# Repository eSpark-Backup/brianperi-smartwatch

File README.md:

# BrianPeri-SmartWatch
 To enhance existing Smart Watch Design and to add support for BLE / WiFi Capability

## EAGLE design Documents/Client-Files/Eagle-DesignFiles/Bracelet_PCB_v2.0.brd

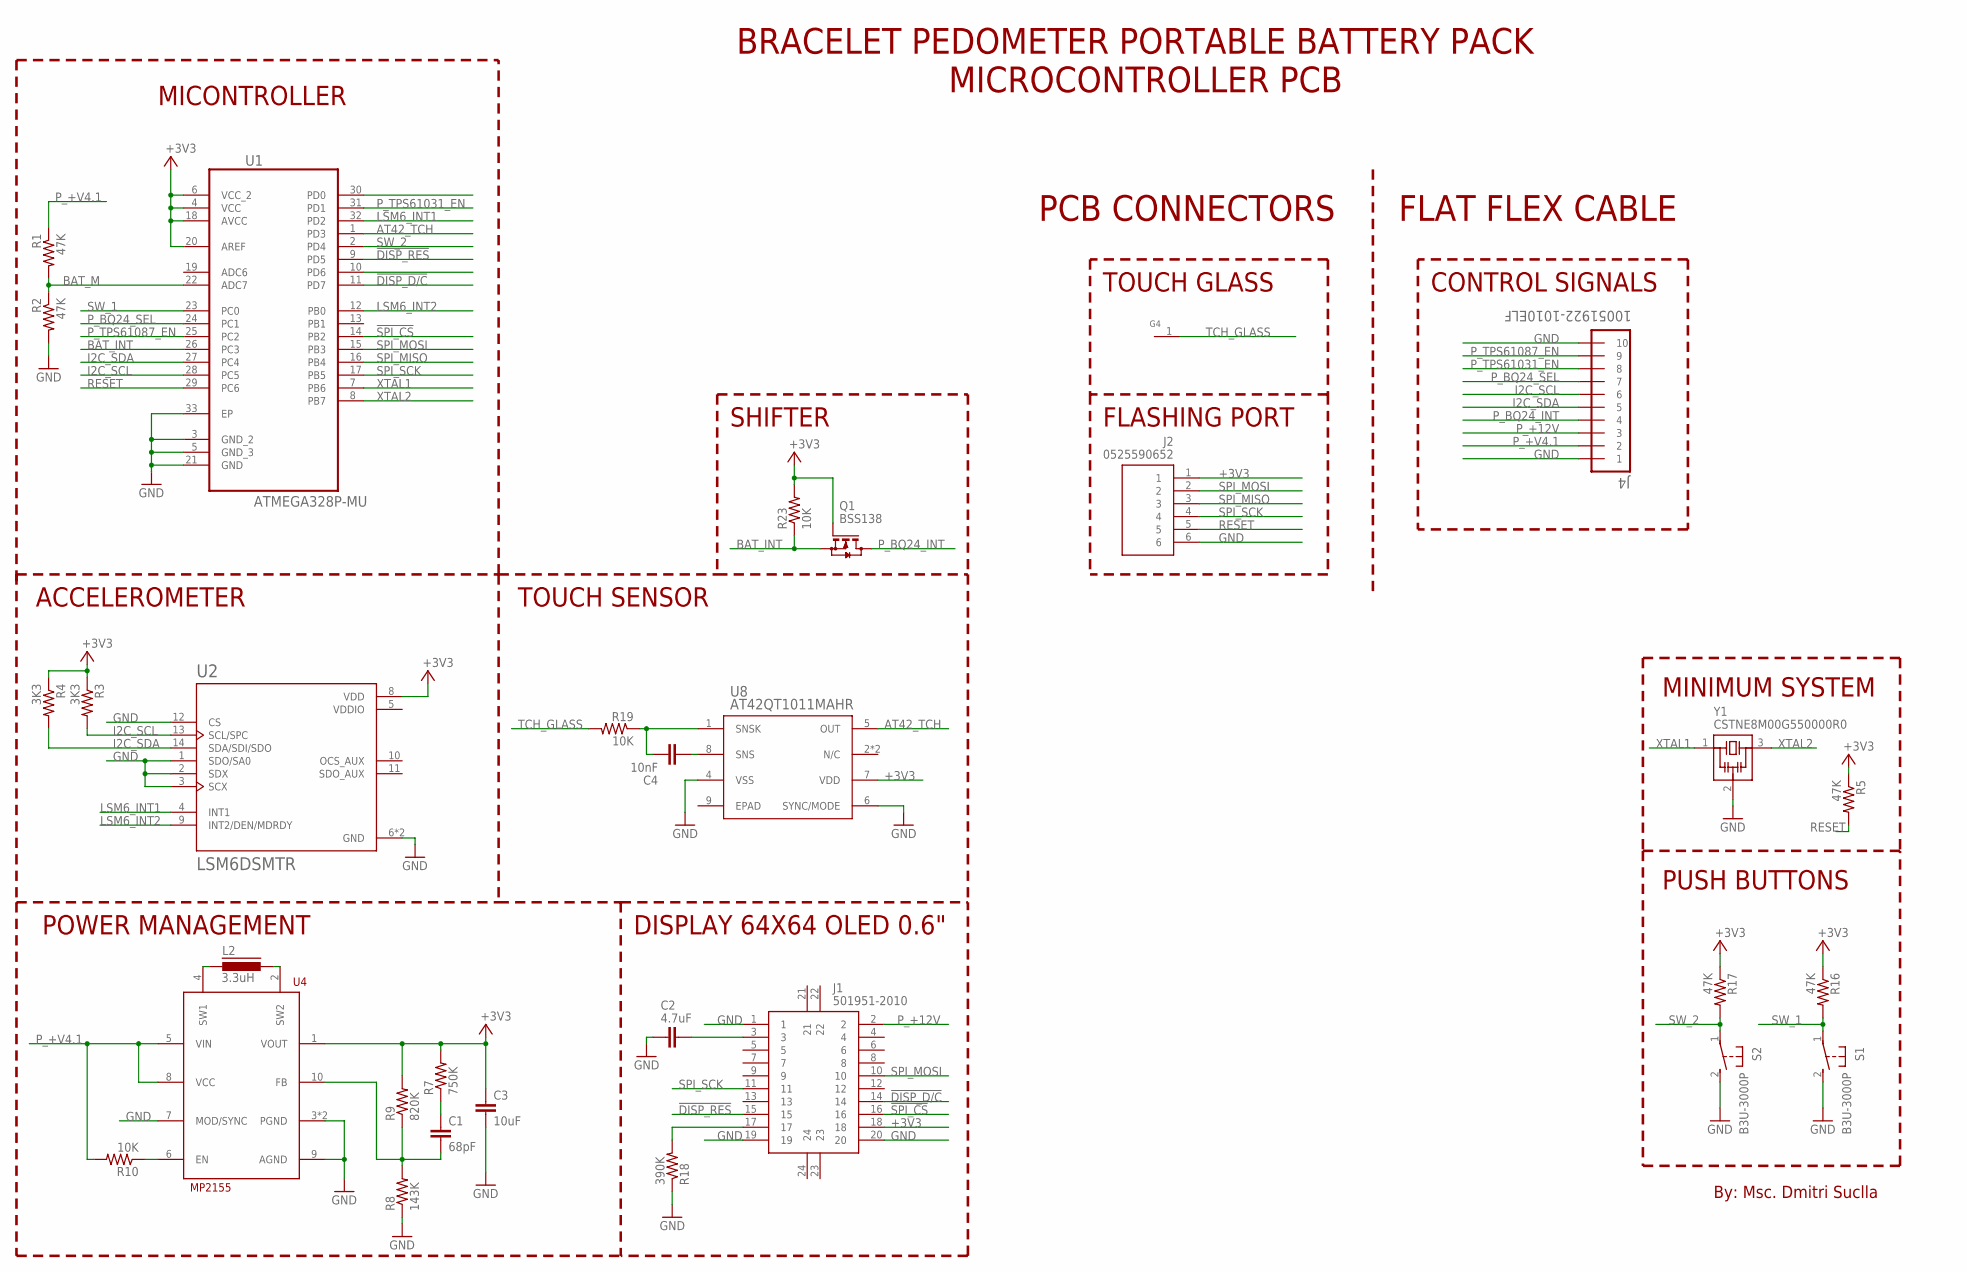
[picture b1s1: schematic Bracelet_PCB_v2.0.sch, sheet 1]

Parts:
C1: 68pF; C0201; MPN GRM0335C1H680JA01D
C2: 4.7uF; C0402
C3: 10uF; C0603; MPN GRM188R61C106KAALJ
C4: 10nF; C0201; MPN GRM033R61E103MA12D
G4: TOUCH_GLASS
J1: 501951-2010; 5019512010
J2: 0525590652
J4: 10051922-1010ELF; FCI_10051922-1010ELF
L2: 3.3uH; 0603(1608)
Q1: BSS138; SOT23
R1, R2, R5, R16, R17: 47K; R0201
R3, R4: 3K3; R0201
R7: 750K; R0201
R8: 143K; R0201
R9: 820K; R0201
R10, R19: 10K; R0201
R18: 390K; R0201
R23: 10K; R0201; MPN ERJ-1GNF1583C
S1, S2: B3U-3000P; SW_B3U-3000P
U1: ATMEGA328P-MU; QFN50P500X500X100-33N
U2: LSM6DSMTR; PQFN50P300X250X86-14N
U4: MP2155; QFN10
U8: AT42QT1011MAHR; 8-UDFN
Y1: CSTNE8M00G550000R0; CSTNE

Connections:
!DISP_D/C: J1.14, U1.11 (PD7)
!DISP_RES: J1.15, U1.9 (PD5)
!SPI_CS: J1.16, U1.14 (PB2)
+3V3: C3.1, J1.18, J2.1, Q1.1 (G), R3.1, R4.1, R5.1, R7.2, R9.2, R16.1, R17.1, R23.2, U1.4 (VCC), U1.6 (VCC_2), U1.18 (AVCC), U1.20 (AREF), U2.8 (VDD), U4.1 (VOUT), U8.7 (VDD)
AT42_TCH: U1.1 (PD3), U8.5 (OUT)
BAT_INT: Q1.2 (S), R23.1, U1.26 (PC3)
BAT_M: R1.2, R2.1, U1.22 (ADC7)
GND: C2.2, C3.2, J1.1, J1.19, J1.20, J2.6, J4.1, J4.10, R2.2, R8.1, R18.1, S1.2, S2.2, U1.3 (GND_2), U1.5 (GND_3), U1.21 (GND), U1.33 (EP), U2.1 (SDO/SA0), U2.2 (SDX), U2.3 (SCX), U2.6 (GND), U2.7 (GND), U2.12 (CS), U4.3 (PGND), U4.7 (MOD/SYNC), U4.9 (AGND), U4.EP (PGND), U8.4 (VSS), U8.6 (SYNC/MODE), Y1.2 (GND)
I2C_SCL: J4.6, R3.2, U1.28 (PC5), U2.13 (SCL/SPC)
I2C_SDA: J4.5, R4.2, U1.27 (PC4), U2.14 (SDA/SDI/SDO)
LSM6_INT1: U1.32 (PD2), U2.4 (INT1)
LSM6_INT2: U1.12 (PB0), U2.9 (INT2/DEN/MDRDY)
unnamed: C1.1, R7.1
unnamed: C1.2, R8.2, R9.1, U4.10 (FB)
unnamed: L2.2, U4.2 (SW2)
unnamed: L2.1, U4.4 (SW1)
unnamed: C4.1, U8.8 (SNS)
unnamed: C2.1, J1.3
unnamed: C4.2, R19.1, U8.1 (SNSK)
unnamed: R10.1, U4.6 (EN)
unnamed: J1.17, R18.2
P_+12V: J1.2, J4.3
P_+V4.1: J4.2, R1.1, R10.2, U4.5 (VIN), U4.8 (VCC)
P_BQ24_INT: J4.4, Q1.3 (D)
P_BQ24_SEL: J4.7, U1.24 (PC1)
P_TPS61031_EN: J4.8, U1.31 (PD1)
P_TPS61087_EN: J4.9, U1.25 (PC2)
RESET: J2.5, R5.2, U1.29 (PC6)
SPI_MISO: J2.3, U1.16 (PB4)
SPI_MOSI: J1.10, J2.2, U1.15 (PB3)
SPI_SCK: J1.11, J2.4, U1.17 (PB5)
SW_1: R16.2, S1.1, U1.23 (PC0)
SW_2: R17.2, S2.1, U1.2 (PD4)
TCH_GLASS: G4.1, R19.2
VDDIO: U2.5 (VDDIO)
XTAL1: U1.7 (PB6), Y1.1 (IN)
XTAL2: U1.8 (PB7), Y1.3 (OUT)

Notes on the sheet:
By: Msc. Dmitri Suclla
MINIMUM SYSTEM
ACCELEROMETER
POWER MANAGEMENT
DISPLAY 64X64 OLED 0.6"
MICONTROLLER
FLASHING PORT
PUSH BUTTONS
TOUCH SENSOR
BRACELET PEDOMETER PORTABLE BATTERY PACK
MICROCONTROLLER PCB
PCB CONNECTORS
CONTROL SIGNALS
FLAT FLEX CABLE
TOUCH GLASS
SHIFTER

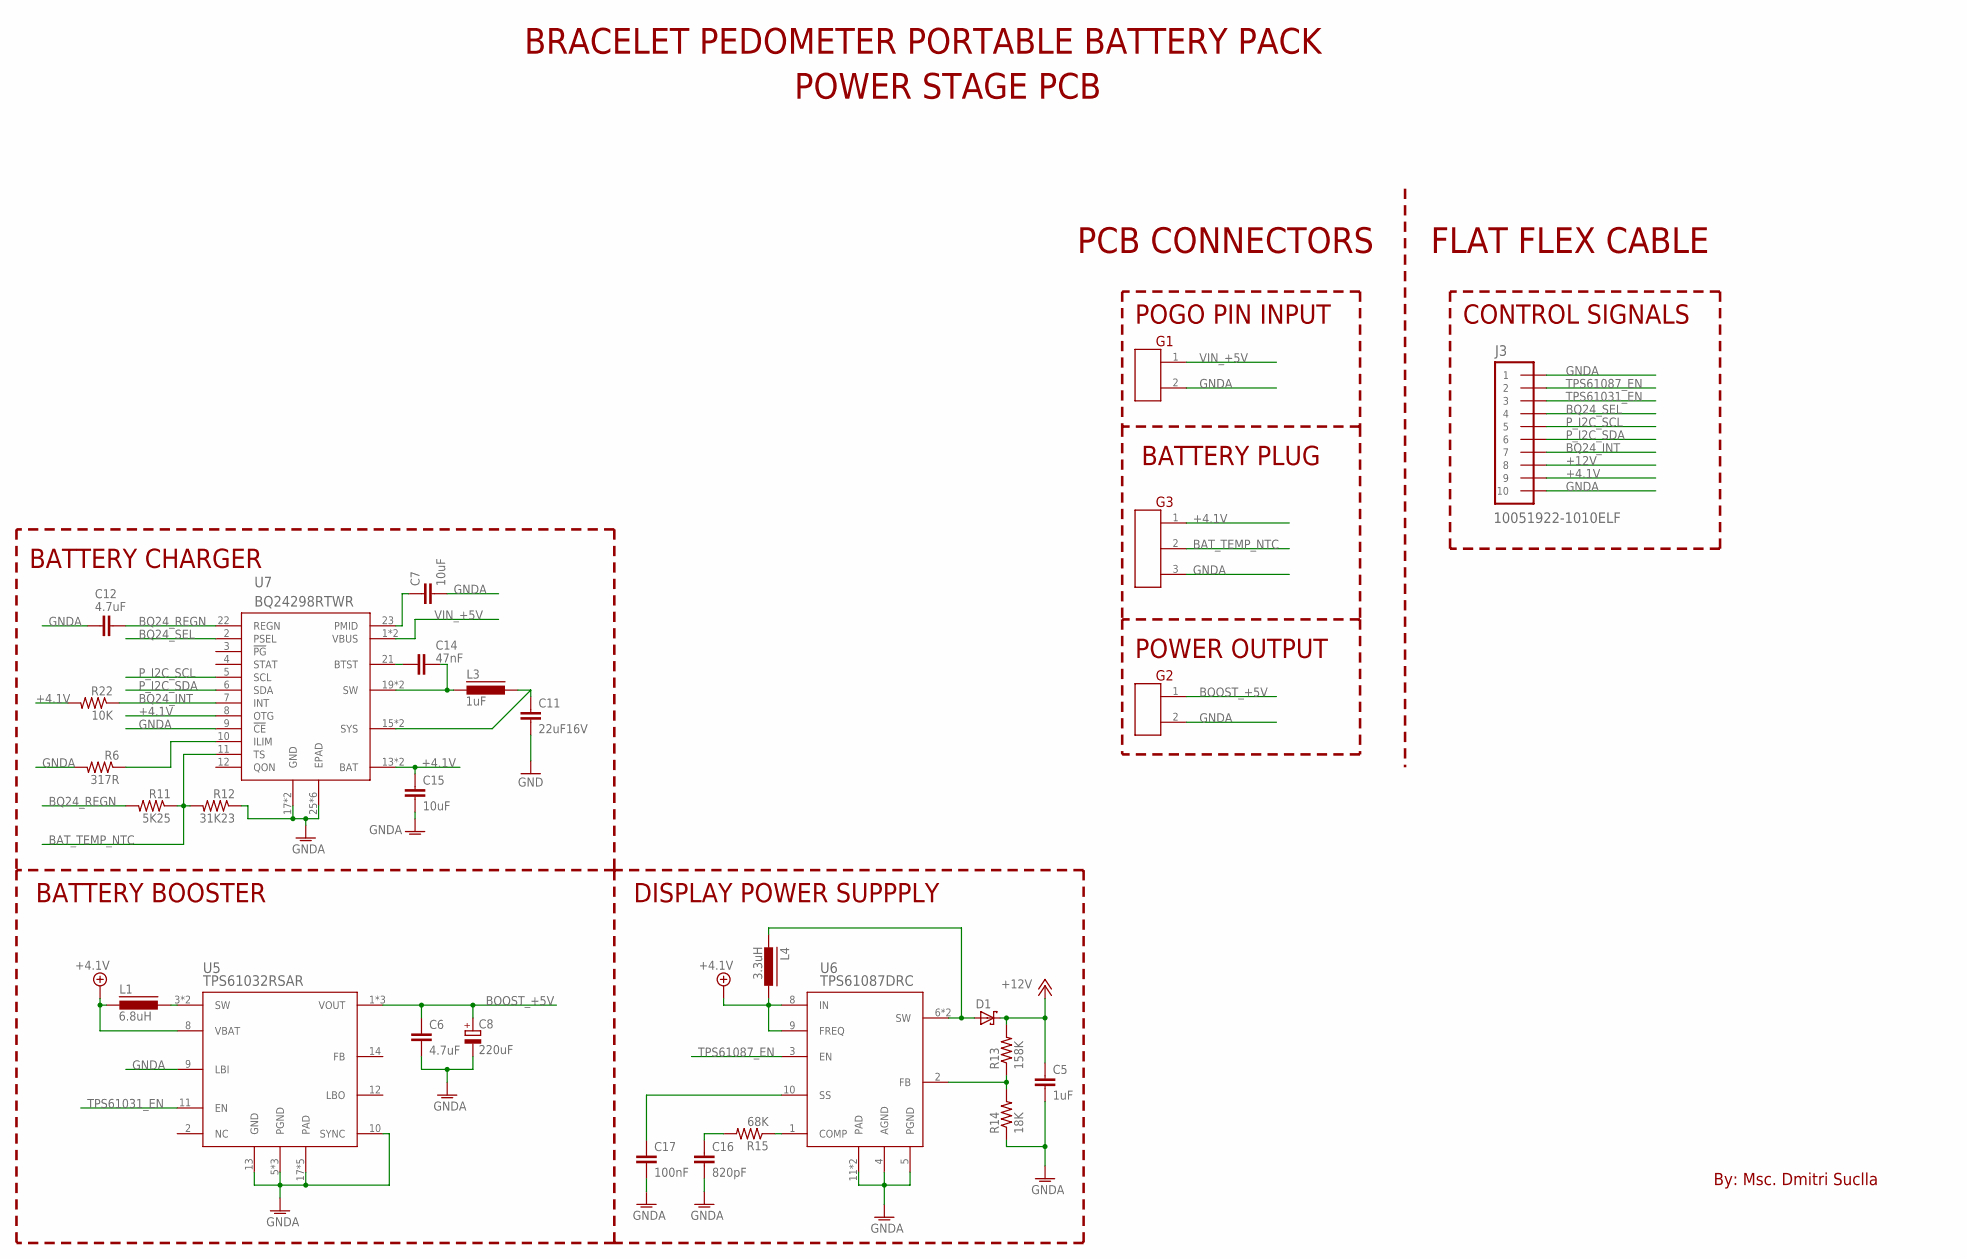
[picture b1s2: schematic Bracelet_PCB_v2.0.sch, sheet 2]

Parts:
C5: 1uF; C0402; MPN CL05A105KA5NQNC
C6, C12: 4.7uF; C0402
C7, C15: 10uF; C0603; MPN GRM188R61C106KAALJ
C8: 220uF; CT3528; MPN F930J227MBA
C11: 22uF16V; C1206
C14: 47nF; C0201
C16: 820pF; C0201; MPN CL03A104KO3NNNC
C17: 100nF; C0201; MPN CL03A104KO3NNNC
D1: CDBU0245CDBU-M; CDBU-M
G1, G2: PIN_HEADER; PIN_HEADER_2P_1.27MM
G3: PIN_HEADER_3; PIN_HEADER_3P
J3: 10051922-1010ELF; FCI_10051922-1010ELF
L1: 6.8uH; SRP5030
L3: 1uF; DFE252012PD
L4: 3.3uH; 0603(1608)
R6: 317R; R0201
R11: 5K25; R0201
R12: 31K23; R0201
R13: 158K; R0201; MPN ERJ-1GNF1583C
R14: 18K; R0201
R15: 68K; R0201
R22: 10K; R0201
U5: TPS61032RSAR; 16-VQFN; MPN TPS61032RSAR
U6: TPS61087DRC; 10-VSON
U7: BQ24298RTWR; VQFN

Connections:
+4.1V: C15.1, G3.1, J3.9, L1.2 (1), L4.2, R22.2, U5.8 (VBAT), U6.8 (IN), U6.9 (FREQ), U7.8 (OTG), U7.13 (BAT), U7.14 (BAT)
+12V: C5.1, D1.C, J3.8, R13.2
BAT_TEMP_NTC: G3.2, R11.1, R12.2, U7.11 (TS)
BOOST_+5V: C6.1, C8.+, G2.1, U5.1 (VOUT), U5.15 (VOUT), U5.16 (VOUT)
BQ24_INT: J3.7, R22.1, U7.7 (INT)
BQ24_REGN: C12.1, R11.2, U7.22 (REGN)
BQ24_SEL: J3.4, U7.2 (PSEL)
GNDA: C5.2, C6.2, C7.2, C8.-, C11.2, C12.2, C15.2, C16.2, C17.2, G1.2, G2.2, G3.3, J3.1, J3.10, R6.2, R12.1, R14.1, U5.5 (PGND), U5.6 (PGND), U5.7 (PGND), U5.9 (LBI), U5.10 (SYNC), U5.13 (GND), U5.17 (PAD), U5.19 (PAD), U5.20 (PAD), U5.21 (PAD), U5.22 (PAD), U6.4 (AGND), U6.5 (PGND), U6.11 (PAD), U6.Y (PAD), U7.9 (!CE), U7.17 (GND), U7.18 (GND), U7.25 (EPAD), U7.G1 (EPAD), U7.G2 (EPAD), U7.G3 (EPAD), U7.G4 (EPAD), U7.G5 (EPAD)
unnamed: R6.1, U7.10 (ILIM)
unnamed: C14.1, L3.1, U7.19 (SW), U7.20 (SW)
unnamed: C14.2, U7.21 (BTST)
unnamed: C7.1, U7.23 (PMID)
unnamed: D1.A, L4.1, U6.6 (SW), U6.7 (SW)
unnamed: L1.1 (2), U5.3 (SW), U5.4 (SW)
unnamed: R13.1, R14.2, U6.2 (FB)
unnamed: R15.1, U6.1 (COMP)
unnamed: C16.1, R15.2
unnamed: C17.1, U6.10 (SS)
unnamed: C11.1, L3.2, U7.15 (SYS), U7.16 (SYS)
P_I2C_SCL: J3.5, U7.5 (SCL)
P_I2C_SDA: J3.6, U7.6 (SDA)
TPS61031_EN: J3.3, U5.11 (EN)
TPS61087_EN: J3.2, U6.3 (EN)
VIN_+5V: G1.1, U7.1 (VBUS), U7.24 (VBUS)

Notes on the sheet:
BATTERY CHARGER
BATTERY BOOSTER
DISPLAY POWER SUPPPLY
POGO PIN INPUT
BATTERY PLUG
BRACELET PEDOMETER PORTABLE BATTERY PACK
POWER STAGE PCB
PCB CONNECTORS
CONTROL SIGNALS
By: Msc. Dmitri Suclla
FLAT FLEX CABLE
POWER OUTPUT

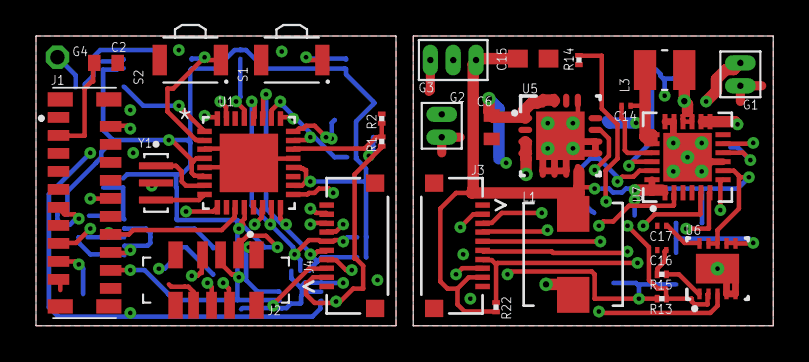
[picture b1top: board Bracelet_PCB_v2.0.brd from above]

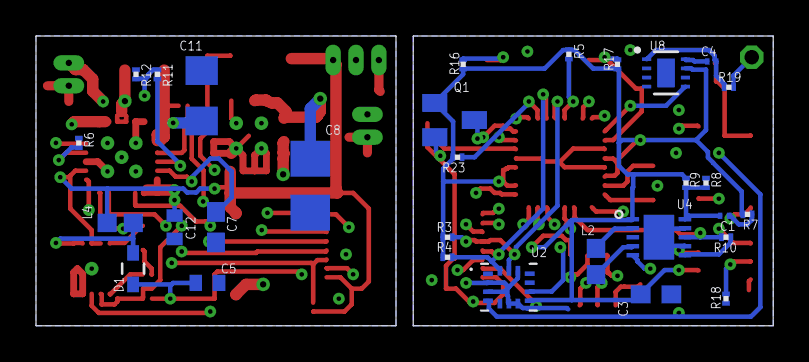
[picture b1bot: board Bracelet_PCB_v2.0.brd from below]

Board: 4 copper layers, 41.0 x 16.1 mm, 59 parts (30 on the bottom side), 60 nets.

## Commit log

2021-07-14 Latest Files and Deliverables
2021-07-15 Latest Design Files and Deliverables of All PCBs
2021-07-15 Latest BOM Main PCB Digikey or LCSC
    BOM me changes baqi han abi kuch parts ki quotation local supplier se ni ayi abi is lye
2021-07-15 Deliverables of all PCBs
2021-07-15 Latest BOM comparision done.
    BOM Abi final ni ha Client ki approvel abi ni ayi is lye.
2021-07-17 Latest Schematic and PCB from Electron Ali
2021-07-17 Cap C19 added successfully Schematic and PCB Both.
2021-07-17 Changes in Controller Section Schematic
2021-07-17 Changes in Controller Section
2021-07-17 Latest Schematics and PCBs
2021-07-17 Controller Schematic Fully Reviewed
2021-07-17 Changes in Power section and parts imported to PCB
2021-07-17 Latest Library Parts addition completed
    issue #7 Resolved.
2021-07-17 Latest Files from Electron Ali
2021-07-19 PCB Routing of Brian PCB
2021-07-19 Routing of Main Board
2021-07-20 Added Previewer Files to .gitignore
2021-07-20 Removed Preview Files
2021-07-25 PCB Review Done. Production and other necessary files created after making some adjustments in PCB.
2021-07-25 PCB Review Done. Production and other necessary files created for Aux v1.0 and Auxv2.0 PCB's.
2021-07-26 Latest Digikey BOM
    Main Board ,AUX 1_PCB and Aux_2 PCB in boards k Digikey BOM Complet ho gaye han.
2021-07-27 All Changes in Mian_PCB are done and made Deliverables of Main_PCB
